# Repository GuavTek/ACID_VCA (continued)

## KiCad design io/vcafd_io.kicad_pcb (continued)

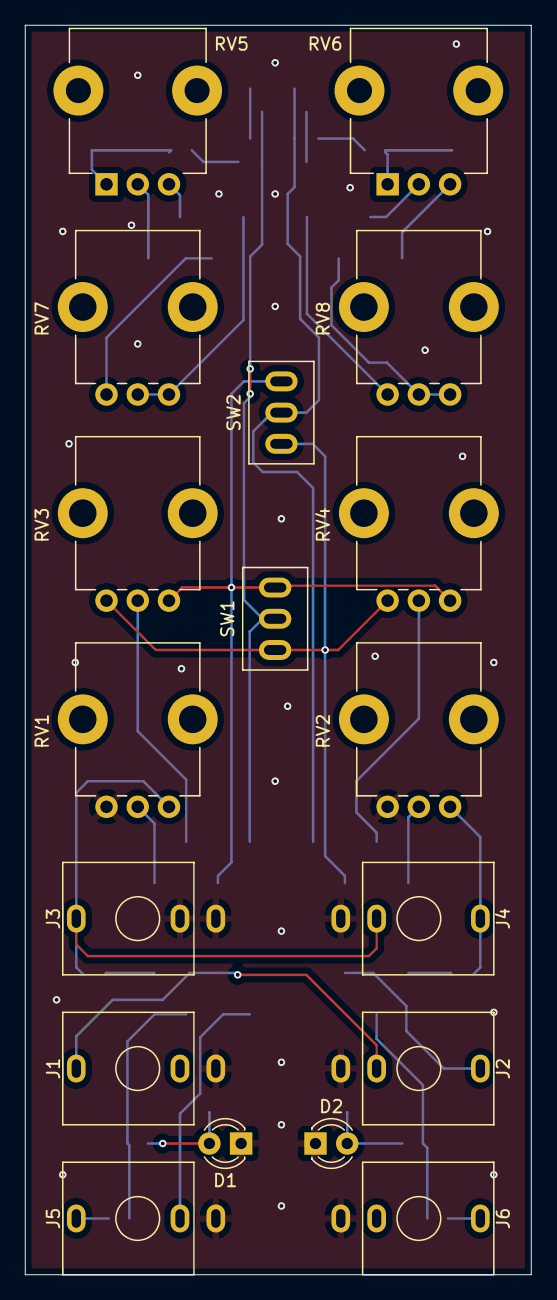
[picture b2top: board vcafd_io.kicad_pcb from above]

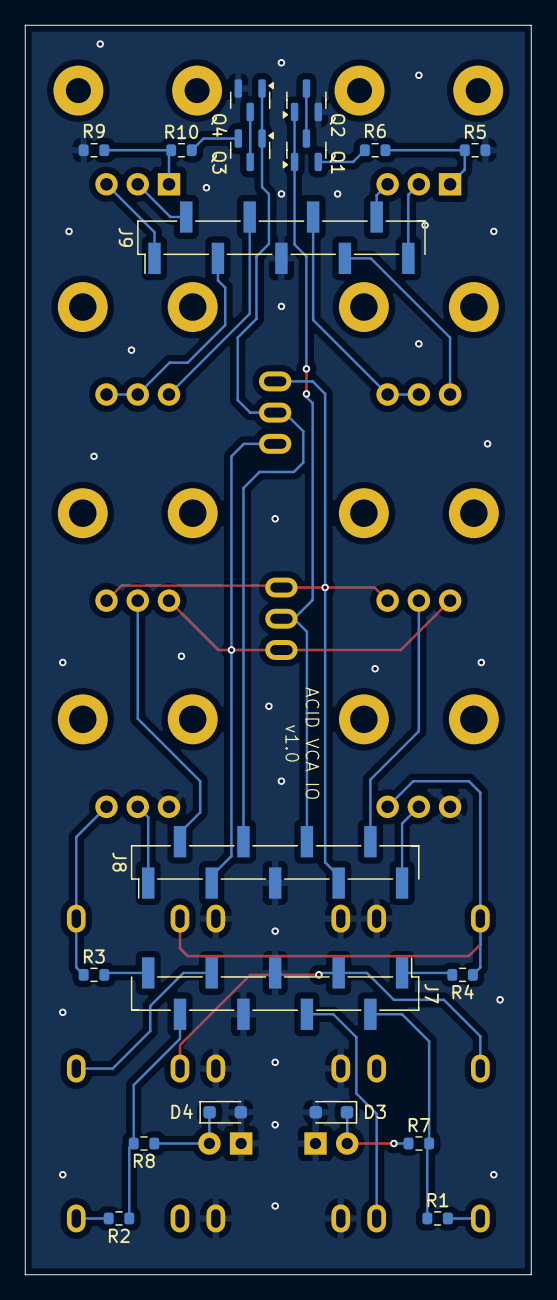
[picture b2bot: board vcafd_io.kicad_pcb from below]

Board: 2 copper layers, 40.5 x 100.0 mm, 37 parts (19 on the bottom side), 36 nets.

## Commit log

2025-03-27 Add license file
2025-03-27 Add gitignore
2025-03-27 Add custom footprints library
2025-03-27 Add initial files
2025-03-27 Update README.md
    Fixed cadlab link
2025-03-29 Tweak resistor values
2025-03-29 Gerbers setup
2025-03-29 Update partnames
2025-03-29 Change to safer resistor value
2025-05-18 Increase Drive silkscreen radius
2025-05-18 Connect CV Tn to ground
2025-05-18 Fixes for v1.1
2025-05-19 Fix CV scaling for new VCA stage
